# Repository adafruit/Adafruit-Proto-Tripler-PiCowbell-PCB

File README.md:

## Adafruit Proto Tripler PiCowbell for Pico and PicoW PCB

<a href="http://www.adafruit.com/products/5967"><br/>
Click here to purchase one from the Adafruit shop</a>

PCB files for the Adafruit Proto Tripler PiCowbell for Pico and PicoW. 

Format is EagleCAD schematic and board layout
* https://www.adafruit.com/product/5967

### Description

The Adafruit Proto Tripler PiCowBell is intended to be treated like a mini solder-less proto plate to simplify programming and sensor or display connectivity for your Raspberry Pi Pico board. Reset button? Yes! STEMMA QT / Qwiic connector for fast I2C? Indeed. Battery with recharging and on/off switch? Affirmative. Built in NeoPixel? Bien sur! EYE SPI connector? Truly! All plug-and-play, so no soldering necessary when used with a Pico H or Pico WH? Here you go!

The Tripler is like if we used a 'Clone Tool' twice on the Proto Under Plate PiCowbell - you get three slots side-by-side, which means you can easily add two 'bell accessories to your Pico or Pico W without soldering on any stacking headers.

LiPoly Battery Charging Support
The Tripler also gives you Lipoly/LiIon support circuitry to take your Pico project on the go. Use any 3.7V/4.2V single-cell Lithium battery with a JST 2-PH connector in the correct polarity. The battery will automagically charge when the Pico is plugged into the USB and switch over seamlessly to battery when USB power is removed.

By default, the charge rate is 500mA for use with 500mAh+ sized batteries. You can cut a jumper to reduce the charge rate to 250mA if using 250mAh to 500mAh battery. So you don't have to unplug the battery often, a slide switch is connected to the Pico Enable pin, so you can disable the Pico's 3.3V power supply completely - this is as close as we can get to 'turning off' the Pico.

Alkaline/NiMH Battery Pack Support
You can also cut a different jumper to disconnect the charger completely from the battery, which means you can use 3xAA or 3xAAA battery packs for alkaline or NiMH battery usage. Of course, you will need an external NiMH charger in that case.

STEMMA QT + EYESPI Connectors

Add sensors and displays in an instant with a 4-Pin JST SH connector that is Qwiic / STEMMA QT compatible for just about any I2C sensor or device we stock. We do not have I2C pullups on the board, but your Qwiic/QT breakout board or accessory likely already has them onboard. If using the Philhower Arduino core, the Wire peripheral is already set up to use IO4 and IO5. If using CircuitPython or MicroPython, you'll need to let the code know to look at 4+5 for SDA+SCL pins.

For colorful high-resolution output, connect any of our EYESPI displays with an 18-pin FPC cable. We connect most of the pins for SPI displays with SD card and touchscreen support. Note that we didn't wire through the Busy or Reset pins so E-Ink displays aren't recommended (they sometimes require those pins for deep-sleep and wakeup)

Double-row Socket Headers
This board has double-row sockets already soldered on; you can plug in your Pico and 'Bell boards directly and access a prototyping area underneath and a second row of socket pins. The second row means you can connect wires just by poking them into the header, either directly to LEDs or buttons or to jumper to a breadboard. So you don't have to look up or count pins; each socket is nicely labeled. There are also 4 mounting holes for easy attachment to an underplate. 

The double-row socket headers we use are 'hollow,' meaning you can connect through the back if desired. Specifically, you can use Pico Stacking Headers to plug into some other device that is expecting Pico pins. Also, in theory, if you soldered pin headers on the 'wrong side' of a Pico, you could plug it up through the bottom.

If you're not mounting this board to something else, we recommend picking up a set of rubber feet to protect your desk.

Features:
* Three 2x20 slim socket headers - plug in your Pico and desired 'Bell and have an extra row of sockets for each pin!
* JST PH connector for LiIon/LiPoly or Alkaline/NiMH battery usage - be sure to cut the "disable charge" jumper to use Alkaline/NiMH batteries.
* LiPoly/LiIon charging circuitry for any 3.7V/4.2V nominal 1-cell battery. Default rate is 500mA, can be set to 250mA by cutting the charge-rate jumper on bottom. Two indicator LEDs let you know if battery is charging (orange) or complete (green)
* Slide switch connected to the Pico Enable pin, which will disable the 3.3V power supply.
* Reset button that sticks out at the end
* JST SH connector for I2C / Stemma QT / Qwiic connection. Or can use it for plain GPIO wiring if you don't have any I2C devices to attach. Provides 3V, GND, IO4 (SDA), and IO5 (SCL)
* There is an extra set of 4 breakout holes next to the JST SH if you want more I2C connections or want to re-assign the I2C port.
* 3 hole-connected strips are in the center areas. You can cut the traces between the holes, but they're intended to be treated like a mini-mini breadboard
* Nearly every pad on the Pico has a duplicate hole pad next to it for solder-jumpering
* The ground pads have white silkscreen rectangles to easily identify, plus one long ground strip near the reset button
* One long strip of connected holes for 3.3V power
* Gold-plated pads for easy soldering

### License

Adafruit invests time and resources providing this open source design, please support Adafruit and open-source hardware by purchasing products from [Adafruit](https://www.adafruit.com)!

Designed by Limor Fried/Ladyada for Adafruit Industries.

Creative Commons Attribution/Share-Alike, all text above must be included in any redistribution. 
See license.txt for additional details.

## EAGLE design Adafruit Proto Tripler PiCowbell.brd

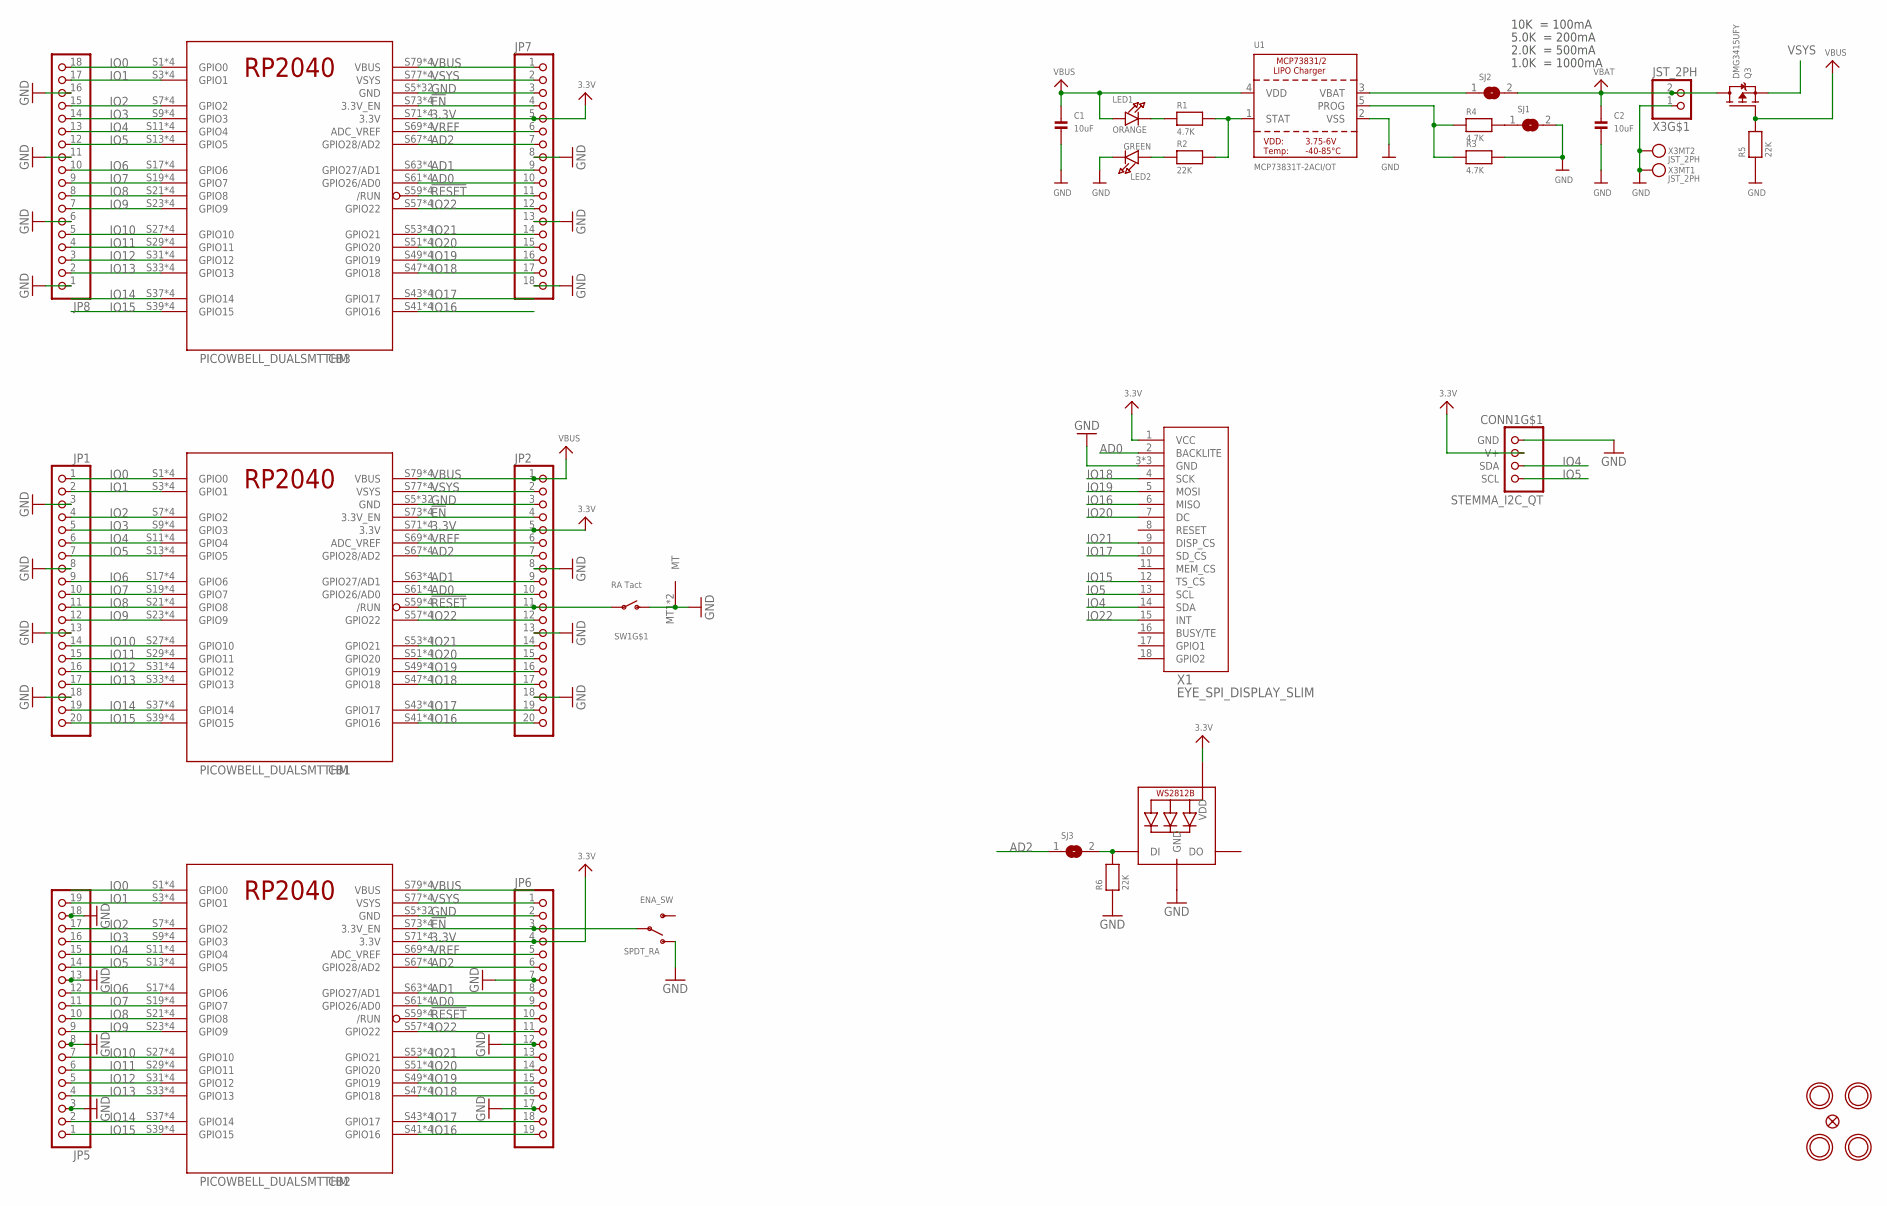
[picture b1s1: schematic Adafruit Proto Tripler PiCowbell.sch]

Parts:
C1, C2: 10uF; 0805-NO
CB1, CB2, CB3: PICOWBELL_DUALSMTTHM
CONN1: STEMMA_I2C_QT; JST_SH4
ENA_SW: SPDT_RA; SPDT_SMT_SSSS811101
FID2: FIDUCIAL_1MM
JP1, JP2: HEADER-1X20_70MIL; 1X20_ROUND_70MIL
JP5, JP6: HEADER-1X19; 1X19_ROUND
JP7, JP8: HEADER-1X18; 1X18_ROUND70
LED1: ORANGE; CHIPLED_0603_NOOUTLINE
LED2: GREEN; CHIPLED_0603_NOOUTLINE
LED3: WS2812B_3535FULL; LED3535_FULLPADS
Q3: DMG3415UFY; DFN2015-3
R1, R3, R4: 4.7K; _0402NO
R2, R5, R6: 22K; _0402NO
SJ1, SJ2, SJ3: SOLDERJUMPERCLOSED; SOLDERJUMPER_CLOSEDWIRE
SW1: RA Tact; SPST_TACTILE_RA
U1: MCP73831T-2ACI/OT; SOT23-5; JLC_ROTATION 0
U$5, U$7, U$15, U$16: MOUNTINGHOLE2.5; MOUNTINGHOLE_2.5_PLATED
X1: EYE_SPI_DISPLAY_SLIM
X3: JST_2PH; JSTPH2_BATT

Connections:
3.3V: CB1.S71 (3.3V), CB1.S72 (3.3V), CB1.T71 (3.3V), CB1.T72 (3.3V), CB2.S71 (3.3V), CB2.S72 (3.3V), CB2.T71 (3.3V), CB2.T72 (3.3V), CB3.S71 (3.3V), CB3.S72 (3.3V), CB3.T71 (3.3V), CB3.T72 (3.3V), CONN1.2 (V+), JP2.5, JP6.4, JP7.5, LED3.2 (VDD), X1.1 (VCC)
!EN: CB1.S73 (3.3V_EN), CB1.S74 (3.3V_EN), CB1.T73 (3.3V_EN), CB1.T74 (3.3V_EN), CB2.S73 (3.3V_EN), CB2.S74 (3.3V_EN), CB2.T73 (3.3V_EN), CB2.T74 (3.3V_EN), CB3.S73 (3.3V_EN), CB3.S74 (3.3V_EN), CB3.T73 (3.3V_EN), CB3.T74 (3.3V_EN), ENA_SW.B, JP2.4, JP6.3, JP7.4
!RESET: CB1.S59 (/RUN), CB1.S60 (/RUN), CB1.T59 (/RUN), CB1.T60 (/RUN), CB2.S59 (/RUN), CB2.S60 (/RUN), CB2.T59 (/RUN), CB2.T60 (/RUN), CB3.S59 (/RUN), CB3.S60 (/RUN), CB3.T59 (/RUN), CB3.T60 (/RUN), JP2.11, JP6.10, JP7.11, SW1.1
AD0: CB1.S61 (GPIO26/AD0), CB1.S62 (GPIO26/AD0), CB1.T61 (GPIO26/AD0), CB1.T62 (GPIO26/AD0), CB2.S61 (GPIO26/AD0), CB2.S62 (GPIO26/AD0), CB2.T61 (GPIO26/AD0), CB2.T62 (GPIO26/AD0), CB3.S61 (GPIO26/AD0), CB3.S62 (GPIO26/AD0), CB3.T61 (GPIO26/AD0), CB3.T62 (GPIO26/AD0), JP2.10, JP6.9, JP7.10, X1.2 (BACKLITE)
AD1: CB1.S63 (GPIO27/AD1), CB1.S64 (GPIO27/AD1), CB1.T63 (GPIO27/AD1), CB1.T64 (GPIO27/AD1), CB2.S63 (GPIO27/AD1), CB2.S64 (GPIO27/AD1), CB2.T63 (GPIO27/AD1), CB2.T64 (GPIO27/AD1), CB3.S63 (GPIO27/AD1), CB3.S64 (GPIO27/AD1), CB3.T63 (GPIO27/AD1), CB3.T64 (GPIO27/AD1), JP2.9, JP6.8, JP7.9
AD2: CB1.S67 (GPIO28/AD2), CB1.S68 (GPIO28/AD2), CB1.T67 (GPIO28/AD2), CB1.T68 (GPIO28/AD2), CB2.S67 (GPIO28/AD2), CB2.S68 (GPIO28/AD2), CB2.T67 (GPIO28/AD2), CB2.T68 (GPIO28/AD2), CB3.S67 (GPIO28/AD2), CB3.S68 (GPIO28/AD2), CB3.T67 (GPIO28/AD2), CB3.T68 (GPIO28/AD2), JP2.7, JP6.6, JP7.7, SJ3.1
GND: C1.2, C2.2, CB1.S5 (GND), CB1.S6 (GND), CB1.S15 (GND), CB1.S16 (GND), CB1.S25 (GND), CB1.S26 (GND), CB1.S35 (GND), CB1.S36 (GND), CB1.S45 (GND), CB1.S46 (GND), CB1.S55 (GND), CB1.S56 (GND), CB1.S65 (GND), CB1.S66 (GND), CB1.S75 (GND), CB1.S76 (GND), CB1.T5 (GND), CB1.T6 (GND), CB1.T15 (GND), CB1.T16 (GND), CB1.T25 (GND), CB1.T26 (GND), CB1.T35 (GND), CB1.T36 (GND), CB1.T45 (GND), CB1.T46 (GND), CB1.T55 (GND), CB1.T56 (GND), CB1.T65 (GND), CB1.T66 (GND), CB1.T75 (GND), CB1.T76 (GND), CB2.S5 (GND), CB2.S6 (GND), CB2.S15 (GND), CB2.S16 (GND), CB2.S25 (GND), CB2.S26 (GND), CB2.S35 (GND), CB2.S36 (GND), CB2.S45 (GND), CB2.S46 (GND), CB2.S55 (GND), CB2.S56 (GND), CB2.S65 (GND), CB2.S66 (GND), CB2.S75 (GND), CB2.S76 (GND), CB2.T5 (GND), CB2.T6 (GND), CB2.T15 (GND), CB2.T16 (GND), CB2.T25 (GND), CB2.T26 (GND), CB2.T35 (GND), CB2.T36 (GND), CB2.T45 (GND), CB2.T46 (GND), CB2.T55 (GND), CB2.T56 (GND), CB2.T65 (GND), CB2.T66 (GND), CB2.T75 (GND), CB2.T76 (GND), CB3.S5 (GND), CB3.S6 (GND), CB3.S15 (GND), CB3.S16 (GND), CB3.S25 (GND), CB3.S26 (GND), CB3.S35 (GND), CB3.S36 (GND), CB3.S45 (GND), CB3.S46 (GND), CB3.S55 (GND), CB3.S56 (GND), CB3.S65 (GND), CB3.S66 (GND), CB3.S75 (GND), CB3.S76 (GND), CB3.T5 (GND), CB3.T6 (GND), CB3.T15 (GND), CB3.T16 (GND), CB3.T25 (GND), CB3.T26 (GND), CB3.T35 (GND), CB3.T36 (GND), CB3.T45 (GND), CB3.T46 (GND), CB3.T55 (GND), CB3.T56 (GND), CB3.T65 (GND), CB3.T66 (GND), CB3.T75 (GND), CB3.T76 (GND), CONN1.1 (GND), ENA_SW.A (O), JP1.3, JP1.8, JP1.13, JP1.18, JP2.3, JP2.8, JP2.13, JP2.18, JP5.3, JP5.8, JP5.13, JP5.18, JP6.2, JP6.7, JP6.12, JP6.17, JP7.3, JP7.8, JP7.13, JP7.18, JP8.1, JP8.6, JP8.11, JP8.16, LED2.C, LED3.4 (GND), R3.2, R5.1, R6.1, SJ1.2, SW1.2 (S), SW1.MT1 (MT), SW1.MT2 (MT), U1.2 (VSS), X1.3 (GND), X1.SUPPORT1 (GND), X1.SUPPORT2 (GND), X3.1, X3.NC1, X3.NC2
IO0: CB1.S1 (GPIO0), CB1.S2 (GPIO0), CB1.T1 (GPIO0), CB1.T2 (GPIO0), CB2.S1 (GPIO0), CB2.S2 (GPIO0), CB2.T1 (GPIO0), CB2.T2 (GPIO0), CB3.S1 (GPIO0), CB3.S2 (GPIO0), CB3.T1 (GPIO0), CB3.T2 (GPIO0), JP1.1, JP8.18
IO1: CB1.S3 (GPIO1), CB1.S4 (GPIO1), CB1.T3 (GPIO1), CB1.T4 (GPIO1), CB2.S3 (GPIO1), CB2.S4 (GPIO1), CB2.T3 (GPIO1), CB2.T4 (GPIO1), CB3.S3 (GPIO1), CB3.S4 (GPIO1), CB3.T3 (GPIO1), CB3.T4 (GPIO1), JP1.2, JP5.19, JP8.17
IO2: CB1.S7 (GPIO2), CB1.S8 (GPIO2), CB1.T7 (GPIO2), CB1.T8 (GPIO2), CB2.S7 (GPIO2), CB2.S8 (GPIO2), CB2.T7 (GPIO2), CB2.T8 (GPIO2), CB3.S7 (GPIO2), CB3.S8 (GPIO2), CB3.T7 (GPIO2), CB3.T8 (GPIO2), JP1.4, JP5.17, JP8.15
IO3: CB1.S9 (GPIO3), CB1.S10 (GPIO3), CB1.T9 (GPIO3), CB1.T10 (GPIO3), CB2.S9 (GPIO3), CB2.S10 (GPIO3), CB2.T9 (GPIO3), CB2.T10 (GPIO3), CB3.S9 (GPIO3), CB3.S10 (GPIO3), CB3.T9 (GPIO3), CB3.T10 (GPIO3), JP1.5, JP5.16, JP8.14
IO4: CB1.S11 (GPIO4), CB1.S12 (GPIO4), CB1.T11 (GPIO4), CB1.T12 (GPIO4), CB2.S11 (GPIO4), CB2.S12 (GPIO4), CB2.T11 (GPIO4), CB2.T12 (GPIO4), CB3.S11 (GPIO4), CB3.S12 (GPIO4), CB3.T11 (GPIO4), CB3.T12 (GPIO4), CONN1.3 (SDA), JP1.6, JP5.15, JP8.13, X1.14 (SDA)
IO5: CB1.S13 (GPIO5), CB1.S14 (GPIO5), CB1.T13 (GPIO5), CB1.T14 (GPIO5), CB2.S13 (GPIO5), CB2.S14 (GPIO5), CB2.T13 (GPIO5), CB2.T14 (GPIO5), CB3.S13 (GPIO5), CB3.S14 (GPIO5), CB3.T13 (GPIO5), CB3.T14 (GPIO5), CONN1.4 (SCL), JP1.7, JP5.14, JP8.12, X1.13 (SCL)
IO6: CB1.S17 (GPIO6), CB1.S18 (GPIO6), CB1.T17 (GPIO6), CB1.T18 (GPIO6), CB2.S17 (GPIO6), CB2.S18 (GPIO6), CB2.T17 (GPIO6), CB2.T18 (GPIO6), CB3.S17 (GPIO6), CB3.S18 (GPIO6), CB3.T17 (GPIO6), CB3.T18 (GPIO6), JP1.9, JP5.12, JP8.10
IO7: CB1.S19 (GPIO7), CB1.S20 (GPIO7), CB1.T19 (GPIO7), CB1.T20 (GPIO7), CB2.S19 (GPIO7), CB2.S20 (GPIO7), CB2.T19 (GPIO7), CB2.T20 (GPIO7), CB3.S19 (GPIO7), CB3.S20 (GPIO7), CB3.T19 (GPIO7), CB3.T20 (GPIO7), JP1.10, JP5.11, JP8.9
IO8: CB1.S21 (GPIO8), CB1.S22 (GPIO8), CB1.T21 (GPIO8), CB1.T22 (GPIO8), CB2.S21 (GPIO8), CB2.S22 (GPIO8), CB2.T21 (GPIO8), CB2.T22 (GPIO8), CB3.S21 (GPIO8), CB3.S22 (GPIO8), CB3.T21 (GPIO8), CB3.T22 (GPIO8), JP1.11, JP5.10, JP8.8
IO9: CB1.S23 (GPIO9), CB1.S24 (GPIO9), CB1.T23 (GPIO9), CB1.T24 (GPIO9), CB2.S23 (GPIO9), CB2.S24 (GPIO9), CB2.T23 (GPIO9), CB2.T24 (GPIO9), CB3.S23 (GPIO9), CB3.S24 (GPIO9), CB3.T23 (GPIO9), CB3.T24 (GPIO9), JP1.12, JP5.9, JP8.7
IO10: CB1.S27 (GPIO10), CB1.S28 (GPIO10), CB1.T27 (GPIO10), CB1.T28 (GPIO10), CB2.S27 (GPIO10), CB2.S28 (GPIO10), CB2.T27 (GPIO10), CB2.T28 (GPIO10), CB3.S27 (GPIO10), CB3.S28 (GPIO10), CB3.T27 (GPIO10), CB3.T28 (GPIO10), JP1.14, JP5.7, JP8.5
IO11: CB1.S29 (GPIO11), CB1.S30 (GPIO11), CB1.T29 (GPIO11), CB1.T30 (GPIO11), CB2.S29 (GPIO11), CB2.S30 (GPIO11), CB2.T29 (GPIO11), CB2.T30 (GPIO11), CB3.S29 (GPIO11), CB3.S30 (GPIO11), CB3.T29 (GPIO11), CB3.T30 (GPIO11), JP1.15, JP5.6, JP8.4
IO12: CB1.S31 (GPIO12), CB1.S32 (GPIO12), CB1.T31 (GPIO12), CB1.T32 (GPIO12), CB2.S31 (GPIO12), CB2.S32 (GPIO12), CB2.T31 (GPIO12), CB2.T32 (GPIO12), CB3.S31 (GPIO12), CB3.S32 (GPIO12), CB3.T31 (GPIO12), CB3.T32 (GPIO12), JP1.16, JP5.5, JP8.3
IO13: CB1.S33 (GPIO13), CB1.S34 (GPIO13), CB1.T33 (GPIO13), CB1.T34 (GPIO13), CB2.S33 (GPIO13), CB2.S34 (GPIO13), CB2.T33 (GPIO13), CB2.T34 (GPIO13), CB3.S33 (GPIO13), CB3.S34 (GPIO13), CB3.T33 (GPIO13), CB3.T34 (GPIO13), JP1.17, JP5.4, JP8.2
IO14: CB1.S37 (GPIO14), CB1.S38 (GPIO14), CB1.T37 (GPIO14), CB1.T38 (GPIO14), CB2.S37 (GPIO14), CB2.S38 (GPIO14), CB2.T37 (GPIO14), CB2.T38 (GPIO14), CB3.S37 (GPIO14), CB3.S38 (GPIO14), CB3.T37 (GPIO14), CB3.T38 (GPIO14), JP1.19, JP5.2
IO15: CB1.S39 (GPIO15), CB1.S40 (GPIO15), CB1.T39 (GPIO15), CB1.T40 (GPIO15), CB2.S39 (GPIO15), CB2.S40 (GPIO15), CB2.T39 (GPIO15), CB2.T40 (GPIO15), CB3.S39 (GPIO15), CB3.S40 (GPIO15), CB3.T39 (GPIO15), CB3.T40 (GPIO15), JP1.20, JP5.1, X1.12 (TS_CS)
IO16: CB1.S41 (GPIO16), CB1.S42 (GPIO16), CB1.T41 (GPIO16), CB1.T42 (GPIO16), CB2.S41 (GPIO16), CB2.S42 (GPIO16), CB2.T41 (GPIO16), CB2.T42 (GPIO16), CB3.S41 (GPIO16), CB3.S42 (GPIO16), CB3.T41 (GPIO16), CB3.T42 (GPIO16), JP2.20, JP6.19, X1.6 (MISO)
IO17: CB1.S43 (GPIO17), CB1.S44 (GPIO17), CB1.T43 (GPIO17), CB1.T44 (GPIO17), CB2.S43 (GPIO17), CB2.S44 (GPIO17), CB2.T43 (GPIO17), CB2.T44 (GPIO17), CB3.S43 (GPIO17), CB3.S44 (GPIO17), CB3.T43 (GPIO17), CB3.T44 (GPIO17), JP2.19, JP6.18, X1.10 (SD_CS)
IO18: CB1.S47 (GPIO18), CB1.S48 (GPIO18), CB1.T47 (GPIO18), CB1.T48 (GPIO18), CB2.S47 (GPIO18), CB2.S48 (GPIO18), CB2.T47 (GPIO18), CB2.T48 (GPIO18), CB3.S47 (GPIO18), CB3.S48 (GPIO18), CB3.T47 (GPIO18), CB3.T48 (GPIO18), JP2.17, JP6.16, JP7.17, X1.4 (SCK)
IO19: CB1.S49 (GPIO19), CB1.S50 (GPIO19), CB1.T49 (GPIO19), CB1.T50 (GPIO19), CB2.S49 (GPIO19), CB2.S50 (GPIO19), CB2.T49 (GPIO19), CB2.T50 (GPIO19), CB3.S49 (GPIO19), CB3.S50 (GPIO19), CB3.T49 (GPIO19), CB3.T50 (GPIO19), JP2.16, JP6.15, JP7.16, X1.5 (MOSI)
IO20: CB1.S51 (GPIO20), CB1.S52 (GPIO20), CB1.T51 (GPIO20), CB1.T52 (GPIO20), CB2.S51 (GPIO20), CB2.S52 (GPIO20), CB2.T51 (GPIO20), CB2.T52 (GPIO20), CB3.S51 (GPIO20), CB3.S52 (GPIO20), CB3.T51 (GPIO20), CB3.T52 (GPIO20), JP2.15, JP6.14, JP7.15, X1.7 (DC)
IO21: CB1.S53 (GPIO21), CB1.S54 (GPIO21), CB1.T53 (GPIO21), CB1.T54 (GPIO21), CB2.S53 (GPIO21), CB2.S54 (GPIO21), CB2.T53 (GPIO21), CB2.T54 (GPIO21), CB3.S53 (GPIO21), CB3.S54 (GPIO21), CB3.T53 (GPIO21), CB3.T54 (GPIO21), JP2.14, JP6.13, JP7.14, X1.9 (DISP_CS)
IO22: CB1.S57 (GPIO22), CB1.S58 (GPIO22), CB1.T57 (GPIO22), CB1.T58 (GPIO22), CB2.S57 (GPIO22), CB2.S58 (GPIO22), CB2.T57 (GPIO22), CB2.T58 (GPIO22), CB3.S57 (GPIO22), CB3.S58 (GPIO22), CB3.T57 (GPIO22), CB3.T58 (GPIO22), JP2.12, JP6.11, JP7.12, X1.15 (INT)
unnamed: R4.2, SJ1.1
unnamed: SJ2.1, U1.3 (VBAT)
unnamed: LED1.C, R1.1
unnamed: R1.2, R2.2, U1.1 (STAT)
unnamed: LED2.A, R2.1
unnamed: R3.1, R4.1, U1.5 (PROG)
unnamed: LED3.1 (DI), R6.2, SJ3.2
VBAT: C2.1, Q3.3 (D), SJ2.2, X3.2
VBUS: C1.1, CB1.S79 (VBUS), CB1.S80 (VBUS), CB1.T79 (VBUS), CB1.T80 (VBUS), CB2.S79 (VBUS), CB2.S80 (VBUS), CB2.T79 (VBUS), CB2.T80 (VBUS), CB3.S79 (VBUS), CB3.S80 (VBUS), CB3.T79 (VBUS), CB3.T80 (VBUS), JP2.1, JP7.1, LED1.A, Q3.1 (G), R5.2, U1.4 (VDD)
VREF: CB1.S69 (ADC_VREF), CB1.S70 (ADC_VREF), CB1.T69 (ADC_VREF), CB1.T70 (ADC_VREF), CB2.S69 (ADC_VREF), CB2.S70 (ADC_VREF), CB2.T69 (ADC_VREF), CB2.T70 (ADC_VREF), CB3.S69 (ADC_VREF), CB3.S70 (ADC_VREF), CB3.T69 (ADC_VREF), CB3.T70 (ADC_VREF), JP2.6, JP6.5, JP7.6
VSYS: CB1.S77 (VSYS), CB1.S78 (VSYS), CB1.T77 (VSYS), CB1.T78 (VSYS), CB2.S77 (VSYS), CB2.S78 (VSYS), CB2.T77 (VSYS), CB2.T78 (VSYS), CB3.S77 (VSYS), CB3.S78 (VSYS), CB3.T77 (VSYS), CB3.T78 (VSYS), JP2.2, JP6.1, JP7.2, Q3.2 (S)

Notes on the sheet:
10K = 100mA
5.0K = 200mA
2.0K = 500mA
1.0K = 1000mA

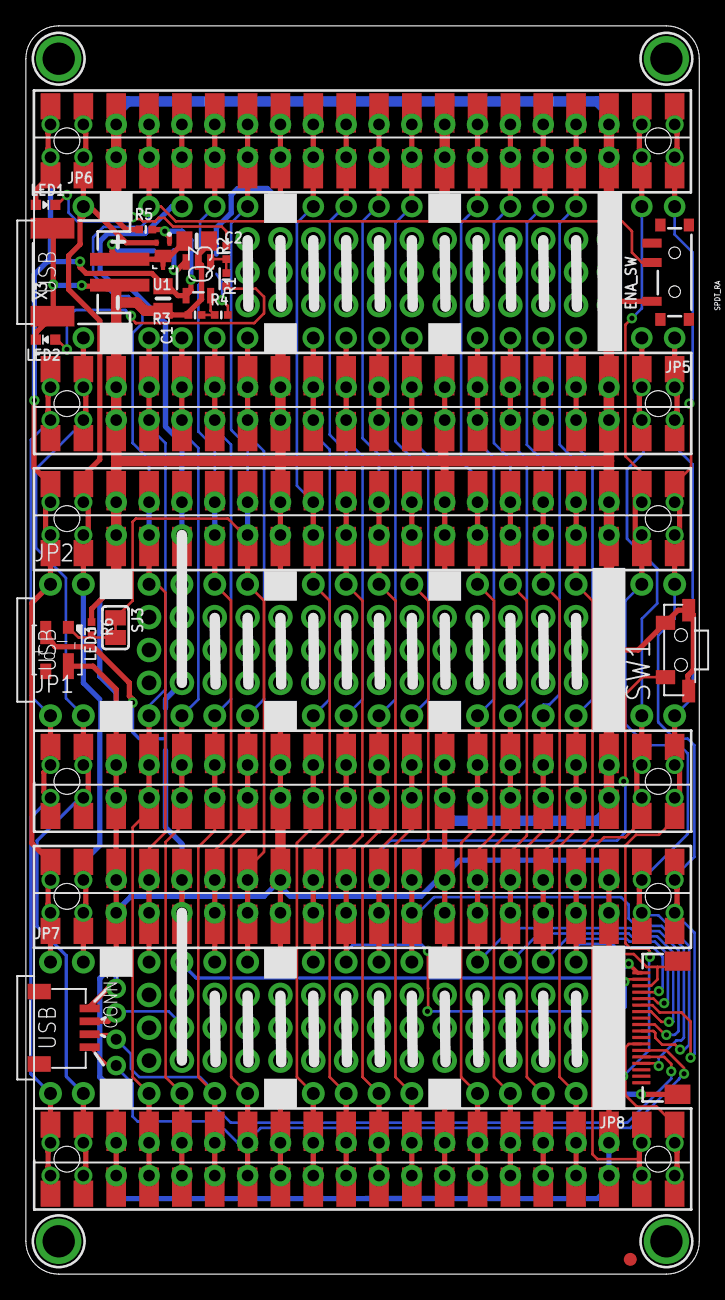
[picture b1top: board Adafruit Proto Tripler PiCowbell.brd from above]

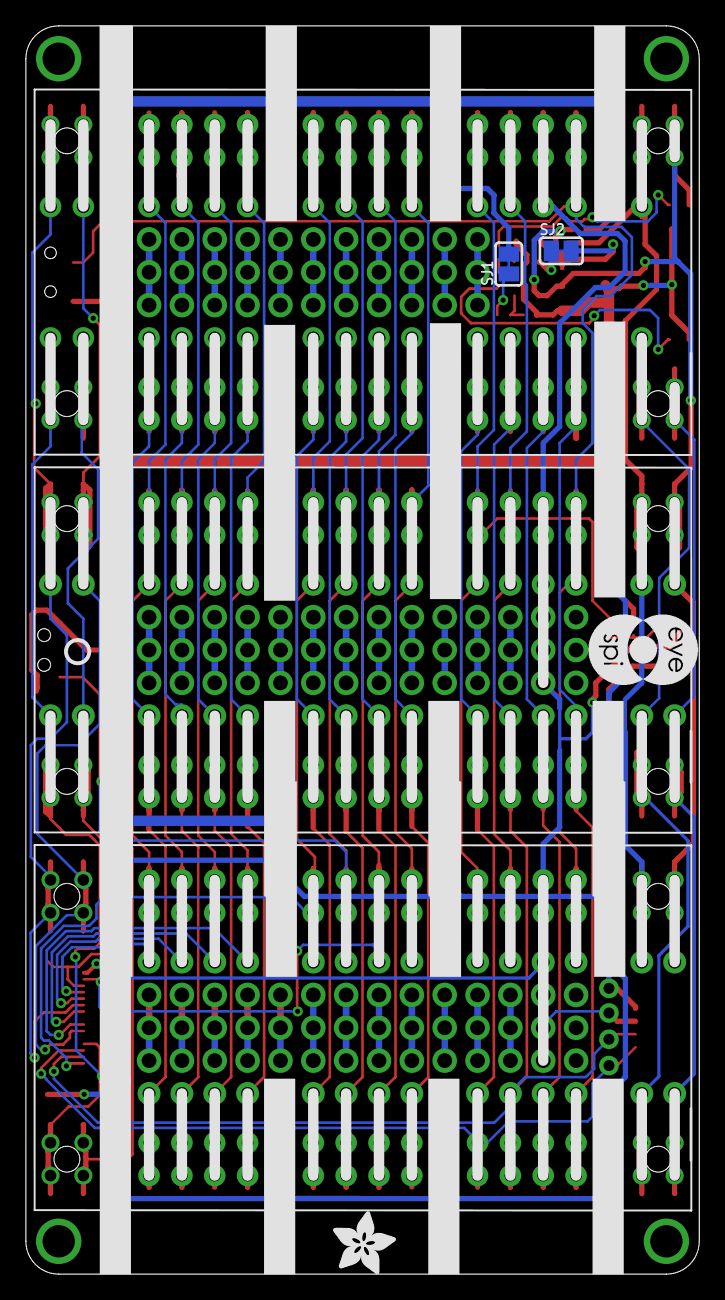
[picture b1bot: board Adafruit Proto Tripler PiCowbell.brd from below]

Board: 2 copper layers, 52.1 x 96.5 mm, 89 parts (19 on the bottom side), 41 nets.

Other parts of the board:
PLABEL0: PLABEL0
PLABEL1: PLABEL1
PLABEL2: PLABEL2
PLABEL3: PLABEL3
PLABEL4: PLABEL4
PLABEL5: PLABEL5
PLABEL6: PLABEL6
PLABEL7: PLABEL7
PLABEL8: PLABEL8
PLABEL9: PLABEL9
PLABEL10: PLABEL10
PLABEL11: PLABEL11
PLABEL12: PLABEL12
PLABEL13: PLABEL13
PLABEL14: PLABEL14
PLABEL15: PLABEL15
PLABEL16: PLABEL16
PLABEL36: PLABEL36
PLABEL37: PLABEL37
PLABEL38: PLABEL38
PLABEL39: PLABEL39
PLABEL40: PLABEL40
PLABEL41: PLABEL41
PLABEL42: PLABEL42
PLABEL43: PLABEL43
PLABEL44: PLABEL44
PLABEL45: PLABEL45
PLABEL48: PLABEL48
PLABEL49: PLABEL49
PLABEL50: PLABEL50
PLABEL51: PLABEL51
PLABEL52: PLABEL52
PLABEL59: PLABEL17
PLABEL60: PLABEL18
PLABEL61: PLABEL19
PLABEL62: PLABEL20
PLABEL63: PLABEL21
PLABEL64: PLABEL22
PLABEL65: PLABEL23
PLABEL66: PLABEL24
PLABEL67: PLABEL25
PLABEL68: PLABEL26
PLABEL69: PLABEL27
PLABEL70: PLABEL28
PLABEL71: PLABEL29
PLABEL72: PLABEL30
PLABEL73: PLABEL31
PLABEL74: PLABEL32
PLABEL75: PLABEL33
PLABEL76: PLABEL34
PLABEL77: PLABEL35
U$6: PCBFEAT-REV-040
U$10: ADAFRUIT_5MM
U$25: EYESPI_MINI_LOGO

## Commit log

2024-05-17 cookiecutter

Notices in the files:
parts and their libraries:
microbuilder: This work is placed in the public domain, and may be freely used for commercial and non-commercial work with the following conditions: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
